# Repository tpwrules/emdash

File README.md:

# Installation Instructions

The code can be built both for an included Mac/Windows/Linux simulator and the LPC11C24 ARM microcontroller. Please follow these directions carefully to learn how to build the code. I assume you have a basic knowledge of command line operation.

## Building the Base

Building the base covers downloading the code and installing Python. Python is required to build the various data files.

#### Installing Git

The Git source control system is used to hold the code. You must install the Git client in order to download the code correctly.

* Download and install Git for your operating system from <https://git-scm.com/downloads>.
    * for the Windows installer, the default options are fine
* Clone the source code
    * open a command prompt and change to the directory you want the source to be downloaded to
    * execute `git clone https://github.com/tpwrules/emdash` to get the code

#### Installing Python

The Python scripting language is used to build data files and run the simulator. These directions have been tested with Python 3.6.6. They will most likely work with 3.5 and 3.6. Python 3.7 is not yet supported.

* Download and install the latest version of Python 3.6 for your operating system from <https://www.python.org/downloads/>
    * For the Windows installer, you must check "Add Python to Path" on the first page
    * Otherwise, the default options are fine

#### Installing Python Packages

Some Python packages are required to build the data files and run the simulator. Fortunately, Python makes them easy to install.

* Open up a command prompt.
* Run the command `python3 -m pip install pypng` or `py -3 -m pip install pypng` (on Windows)
* If python isn't found, close and re-open the command prompt.

#### Testing the Base

Now that the base has been prepared, it's time to test to make sure it works.

* Open a command prompt
* Change directories to the `dashboard` directory within the downloaded code
    * Hint: you can drag that folder into the command prompt instead of typing out its location
* Run the command `build_src_gen.py`. If you see the message `SOURCE GENERATED SUCCESSFULLY`, the base has been successfully built!

## Building for LPC11C24

Building for LPC11C24 requires a working install of the base. It does not require the simulator. I use the free MCUXpresso IDE for development on the LPC11C24. You must install it and import the project in order to deploy the code onto the chip.

#### Installing MCUXpresso
You can download the MCUXpresso 10.1.1 installer from [here](https://www.nxp.com/support/developer-resources/software-development-tools/mcuxpresso-software-and-tools/mcuxpresso-integrated-development-environment-ide:MCUXpresso-IDE?tab=Design_Tools_Tab). Click the Download button, log in with an NXP account (required), then select 10.1.1 under the Previous tab. Version 10.2 seems to be broken, so don't use it.

Run the installer using all the default options. Make a workspace in your favorite place.

#### Importing the code
Now that the projects are downloaded, they can be imported into MCUXpresso.

* Select File -> Import
* Select to import Git -> Projects from Git and click Next
* Select the Existing local repository source and click Next.
* Click Add... and then Browse...
* Select the `emdash` folder in the code you downloaded and click OK.
* Check the `emdash\.git` repository in the results list and click Finish. 
* Select the `emdash` repository in the repository list and click Next twice, then Finish. Code import is now complete.

#### Building the code
Build the code for the chip by selecting the dash_11c24 project in the left pane and clicking the hammer icon in the top bar. If everything works, you will see a blue `Build finished` in the bottom window.

You can then use the green bug icon to program the chip with the code and enter the debugger. The first time you click the button, you will be asked to create a run configuration. Double-click the `C/C++ (NXP Semiconductor)` option in the left pane to create the correct configuration, then click Debug in the bottom to start it. Once this is done, the green button will launch the correct configuration automatically.

## Building for Simulation
A custom simulator is included which runs the same code that is downloaded on the chip. Running the simulator requires a working install of the base, but does not require MCUXpresso or the other LPC11C24 stuff. It also requires a compatible install of the Visual C++ Build Tools, which use several gigabytes of disk space.

#### Installing Python Packages
The simulator requires some additional Python packages to operate.

* Open a command prompt
* Run the command `python3 -m pip install cffi numpy pygame` or `py -3 -m pip install cffi numpy pygame` (on Windows)

#### Installing Visual C++ Build Tools
The build tools provide the compiler used to compile the application for simulation. You try to compile the application to see if the tools are already installed. If they are not, an installation is necessary.

* Open a command prompt
* Change directories to the `dashboard/pc` directory inside the code
* Run the command `build_pc_app.py`. If there are no errors, you're finished building for simulation
* If it says you need to install Visual C++ 14.0, a compatible version of the build tools could not be found.
* Download the Build Tools for Visual Studio 2017 installer from <https://go.microsoft.com/fwlink/?linkid=840931>.
* Once the main installer loads, check 'Visual C++ build tools' under the 'Workloads' tab and click Install
* Wait quite a while. Once finished, try to run the script again. If it says `PC APP BUILT SUCCESSFULLY`, you've successfully built the simulator and you should be able to run it by running `pc_app.py`.

## Installing the CAN libraries
The LPC11C24 code has a bootloader and PC-based programming application so that the devices can be reprogrammed over CAN. The simulator can generate and receive CAN messages for test purposes. Both of these functionalities require the installation of CAN libraries for Python and the appropriate hardware drivers.

#### Installing the Python libraries
* Open up a command prompt.
* Run the command `python3 -m pip install python-can` or `py -3 -m pip install python-can` (on Windows)

#### Installing the Vector drivers
The program uses Vector CAN interfaces. You can try to run the programming application to see if the correct drivers are already installed. If the Vector interface drivers are not installed, they are available [here](https://vector.com/vi_downloadcenter_en.html?type=Driver&formular_treffer_submit=1). Download the latest version of "Vector Driver Setup".

* Open a command prompt
* Change directories to balsdjfsldf
* Run `the bootloader program`. If you see the error message `The Vector API has not been loaded`, the drivers must be installed. If you see a different error, continue to dkjfas;.
* Run the Vector Driver Setup installer program. Select and install the interface types you wish to use.
* Driver installation is now complete.

#### Configuring the Vector drivers
The Vector drivers require you to create an application configuration, which tells the application which hardware to use.

* Open the Windows Control Panel and select the Vector Hardware option.
* Select Application -> Add in the top bar to create a new application.
* Name the application `emdash`, set 1 CAN channel and 0 for all other types, and click OK.
* Select Application -> emdash in the left pane, then right-click on CAN 1 and select the interface you wish to use. You may have to plug in your interface first.
* Close the window. Configuration is now complete.

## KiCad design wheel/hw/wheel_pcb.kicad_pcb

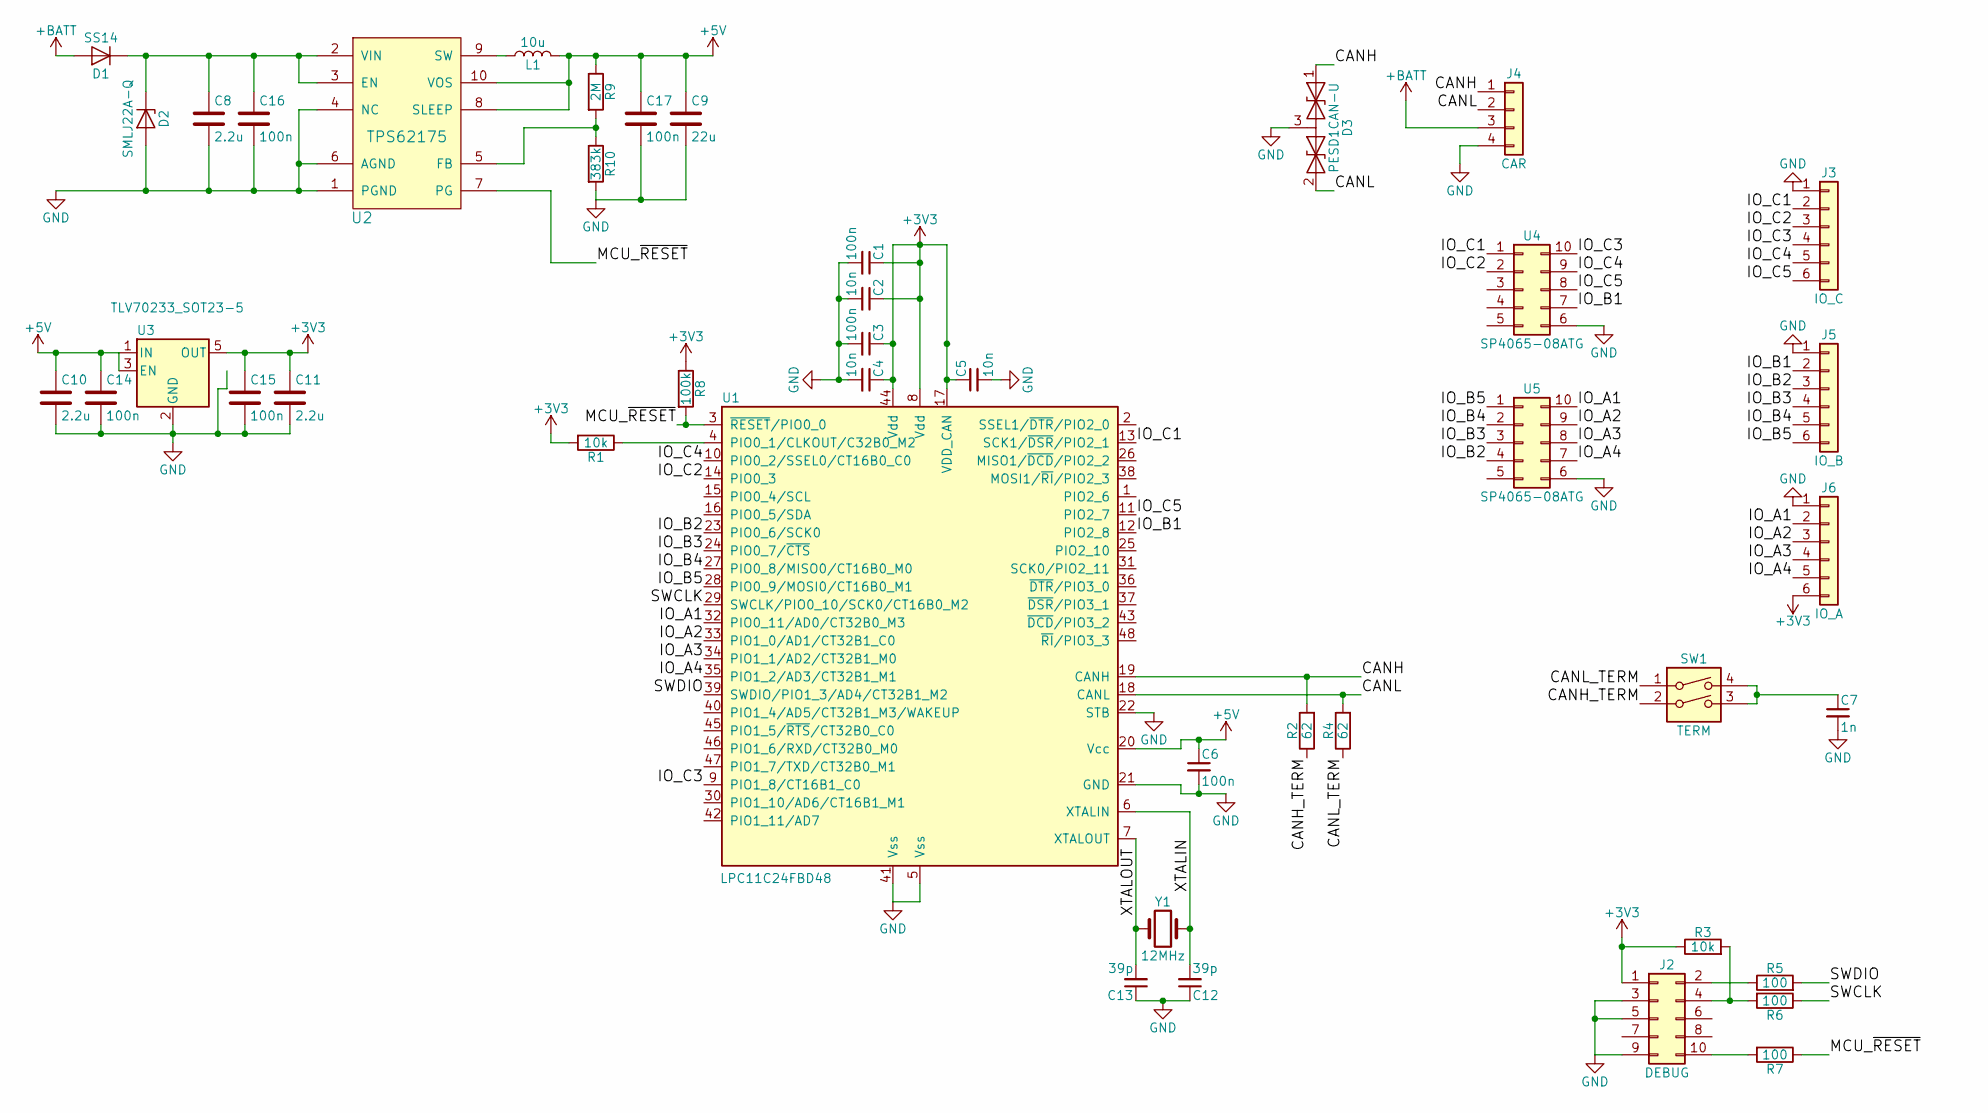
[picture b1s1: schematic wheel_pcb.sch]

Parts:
C1, C3, C6, C14, C15, C16, C17: 100n; C_0603
C2, C4, C5: 10n; C_0603
C7: 1n; C_0603
C8, C10, C11: 2.2u; C_0603
C9: 22u; C_0603
C12, C13: 39p; C_0603
D1: SS14; D_SMA_Handsoldering
D2: SMLJ22A-Q; D_SMC
D3: PESD1CAN-U; SOT-23
J2: DEBUG; Pin_Header_Angled_2x05_Pitch1.27mm_AMPHENOL_SHROUDED
J3: IO_C; Pin_Header_Angled_1x06_Pitch2.54mm
J4: CAR; Pin_Header_Angled_1x04_Pitch2.54mm
J5: IO_B; Pin_Header_Angled_1x06_Pitch2.54mm
J6: IO_A; Pin_Header_Angled_1x06_Pitch2.54mm
L1: 10u; Coilcraft_LPS4018
R1, R3: 10k; R_0603
R2, R4: 62; R_0603
R5, R6, R7: 100; R_0603
R8: 100k; R_0603
R9: 2M; R_0603
R10: 383k; R_0603
SW1: TERM; SW_DIP_x2_W7.62mm_Slide
U1: LPC11C24FBD48; LQFP-48_7x7mm_Pitch0.5mm
U2: TPS62175; DQC
U3: TLV70233_SOT23-5; SOT-23-5
U4, U5: SP4065-08ATG; MSOP-10_3x3mm_Pitch0.5mm
Y1: 12MHz; Crystal_SMD_HC49-SD

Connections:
+3V3: C1.1, C2.1, C3.1, C4.1, C5.1, C11.1, C15.1, J2.1, J6.6, R1.2, R3.1, R8.1, U1.8 (Vdd), U1.17 (VDD_CAN), U1.44 (Vdd), U3.5 (OUT)
+5V: C6.1, C9.1, C10.1, C14.1, C17.1, L1.2, R9.1, U1.20 (Vcc), U2.8 (SLEEP), U2.10 (VOS), U3.1 (IN), U3.3 (EN)
+BATT: D1.2 (A), J4.3
/CANH: D3.1 (A1), J4.1, R2.2, U1.19 (CANH)
/CANH_TERM: R2.1, SW1.2
/CANL: D3.2 (A2), J4.2, R4.2, U1.18 (CANL)
/CANL_TERM: R4.1, SW1.1
/IO_A1: J6.2, U1.32 (PIO0_11/AD0/CT32B0_M3), U5.10
/IO_A2: J6.3, U1.33 (PIO1_0/AD1/CT32B1_C0), U5.9
/IO_A3: J6.4, U1.34 (PIO1_1/AD2/CT32B1_M0), U5.8
/IO_A4: J6.5, U1.35 (PIO1_2/AD3/CT32B1_M1), U5.7
/IO_B1: J5.2, U1.12 (PIO2_8), U4.7
/IO_B2: J5.3, U1.23 (PIO0_6/SCK0), U5.4
/IO_B3: J5.4, U1.24 (PIO0_7/~CTS), U5.3
/IO_B4: J5.5, U1.27 (PIO0_8/MISO0/CT16B0_M0), U5.2
/IO_B5: J5.6, U1.28 (PIO0_9/MOSI0/CT16B0_M1), U5.1
/IO_C1: J3.2, U1.13 (SCK1/~DSR~/PIO2_1), U4.1
/IO_C2: J3.3, U1.14 (PIO0_3), U4.2
/IO_C3: J3.4, U1.9 (PIO1_8/CT16B1_C0), U4.10
/IO_C4: J3.5, U1.10 (PIO0_2/SSEL0/CT16B0_C0), U4.9
/IO_C5: J3.6, U1.11 (PIO2_7), U4.8
/MCU_~RESET: R7.1, R8.2, U1.3 (~RESET~/PIO0_0), U2.7 (PG)
/SWCLK: R6.1, U1.29 (SWCLK/PIO0_10/SCK0/CT16B0_M2)
/SWDIO: R5.2, U1.39 (SWDIO/PIO1_3/AD4/CT32B1_M2)
/XTALIN: C12.2, U1.6 (XTALIN), Y1.1
/XTALOUT: C13.2, U1.7 (XTALOUT), Y1.2
GND: C1.2, C2.2, C3.2, C4.2, C5.2, C6.2, C7.2, C8.2, C9.2, C10.2, C11.2, C12.1, C13.1, C14.2, C15.2, C16.2, C17.2, D2.2 (A), D3.3 (common), J2.3, J2.5, J2.9, J3.1, J4.4, J5.1, J6.1, R10.2, U1.5 (Vss), U1.21 (GND), U1.22 (STB), U1.41 (Vss), U2.1 (PGND), U2.4 (NC), U2.6 (AGND), U3.2 (GND), U3.4 (NC), U4.6, U5.6
unnamed: C7.1, SW1.3, SW1.4
unnamed: C8.1, C16.1, D1.1 (K), D2.1 (K), U2.2 (VIN), U2.3 (EN)
unnamed: J2.2, R5.1
unnamed: J2.4, R3.2, R6.2
unnamed: J2.10, R7.2
unnamed: L1.1, U2.9 (SW)
unnamed: R1.1, U1.4 (PIO0_1/CLKOUT/C32B0_M2)
unnamed: R9.2, R10.1, U2.5 (FB)

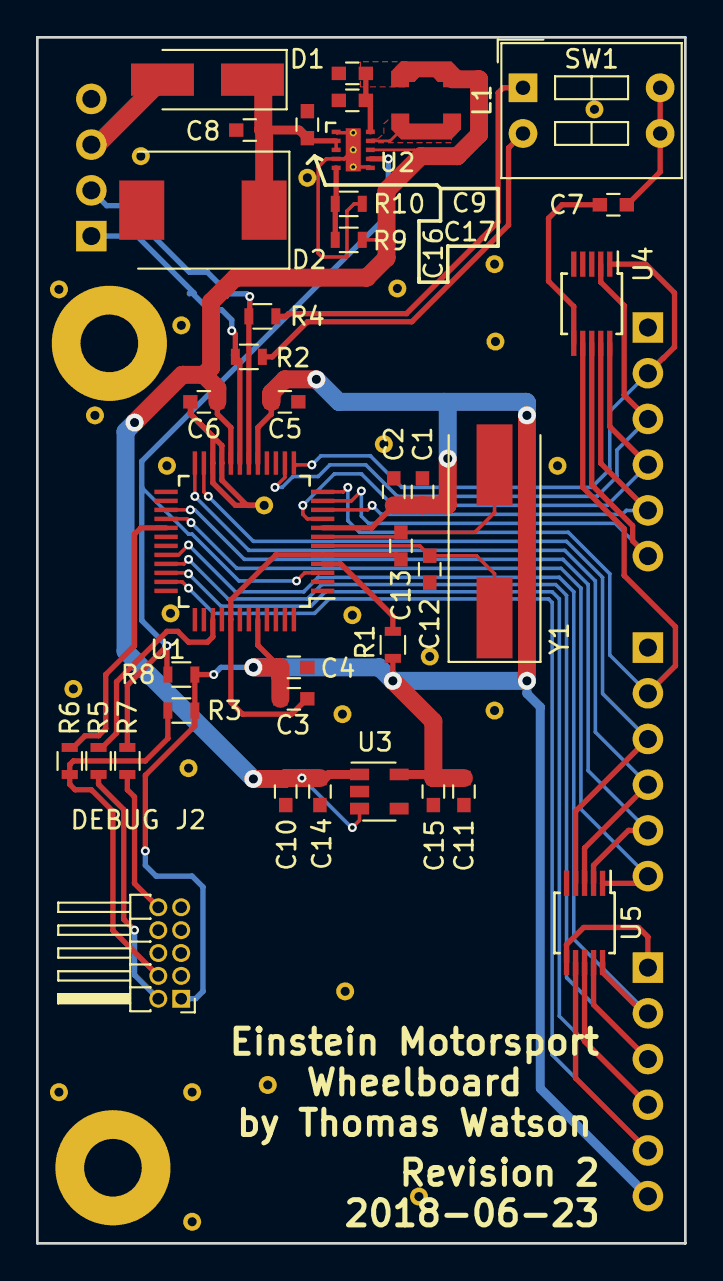
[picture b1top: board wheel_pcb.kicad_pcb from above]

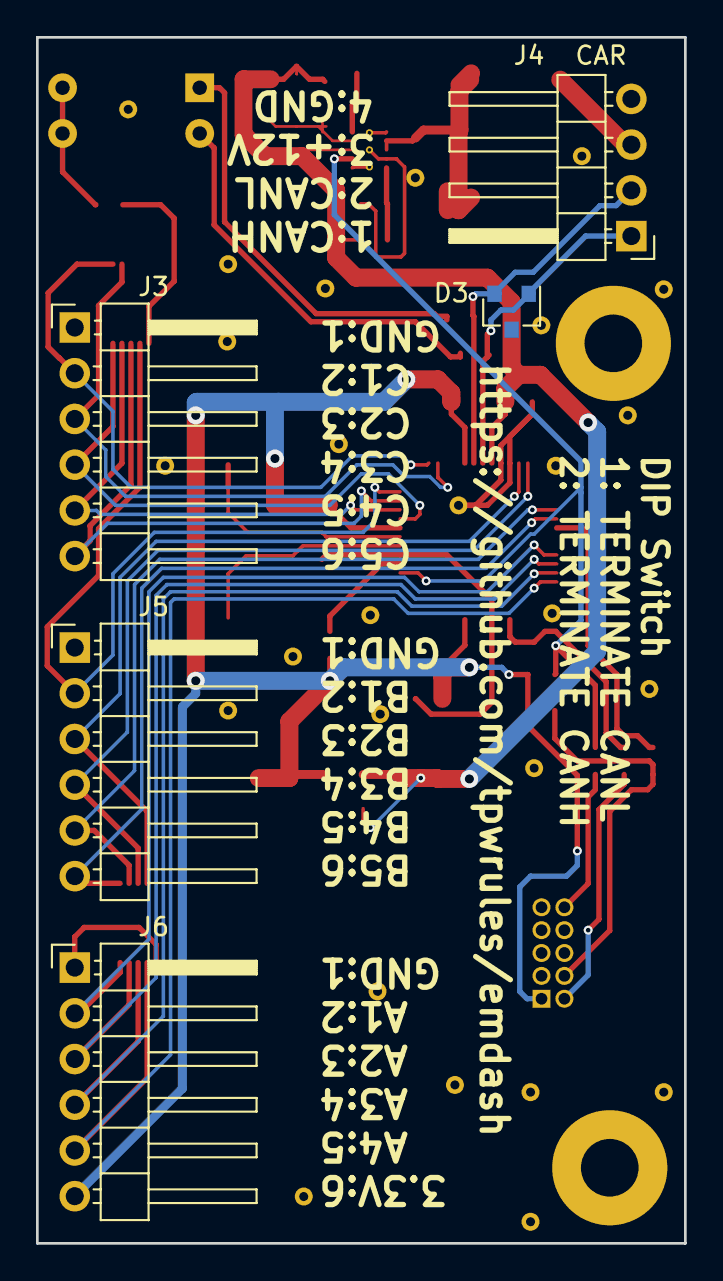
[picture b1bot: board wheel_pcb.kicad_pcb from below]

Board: 2 copper layers, 36.0 x 67.0 mm, 43 parts (5 on the bottom side), 35 nets.

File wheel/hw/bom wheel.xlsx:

Designation | Description | Mfg/# | Mouser # | RS # | Farnell # | Substitute | Quantity
C5, C4, C2 | 10nF 0603 >5V | Any | Any | Any | Any | Yes | 3
C6, C3, C1, C15, C17, C16, C14 | 100nF 0603 >5V | Any | Any | Any | Any | Yes | 7
C7 | 1nF 0603 | Any | Any | Any | Any | Yes | 1
C8, C10, C11 | 2.2uF 0603 X5R 25V | Murata GRM188R61E225ME84D | 81-GRM188R61E225ME4D | 915-9139 | 2576752 | Yes | 3
C9 | 22uF 0603 X5R 10V | Murata GRM188R61A226ME15D | 81-GRM188R61A226ME5D | 884-7258 | 2426957 | Yes | 1
C12, C13 | 39pF 0603 16V | Vishay VJ0603A390GXJPW1BC | 77-VJ0603A390GXJPBC | 652-0055 | 2496903 | Yes | 2
D1 | 40V 1A SMA Schottky Diode | Vishay SS14-E3/61T | 625-SS14-E3 | 638-7915 | 9551280 | Yes | 1
D2 | 22V 3kW Unidirectional SMA TVS Diode | Bourns SMLJ22A-Q | 652-SMLJ22A-Q | 172-3265 | 2839633 | Yes | 1
D3 | CAN bus TVS Diode | Nexperia PESD1CAN-UX | 771-PESD1CANUX | 136-4886 | 2357118 | No | 1
J2 | 2x5 1.27mm right angle shrouded male header | Samtec SHF-105-01-L-D-RA | 649-200215120001T4LF | 901-1850 | 2505002 | Yes | 1
J3, J5, J6 | 1x6 2.54mm connector | TE 281698-6 | 571-281698-6 | 532-125 | 1205994 | No | 3
J4 | 1x4 2.54mm connector | TE 281698-4 | 571-281698-4 | 532-103 | 1205992 | No | 1
L1 | 10uH SMD 1.3A 200mΩ | Coilcraft LPS4018-103MRB | 994-LPS4018-103MRB | Unavailable | 2408105 | No | 1
R2, R4 | 62Ω 0603 | Panasonic ERJ-3EKF62R0V | 667-ERJ-3EKF62R0V | 122-9377 | 2303039 | Yes | 2
R3, R1 | 10kΩ 0603 | Any | Any | Any | Any | Yes | 2
R5, R6, R7 | 100Ω 0603 | Any | Any | Any | Any | Yes | 3
R8 | 100kΩ 0603 | Any | Any | Any | Any | Yes | 1
R9 | 2MΩ 0603 1/10W 1% | Vishay CRCW06032M00FKEB | 71-CRCW06032M00FKEB | 679-0169 | 2447325 | Yes | 1
R10 | 383kΩ 0603 1/10W 1% | Yaego AC0603FR-07383KL | 603-AC0603FR-07383KL | Unavailable | 2138556 | Yes | 1
SW1 | 2 position 2.54mm DIP switch | APM NDS02V | 642-NDS02V | 877-2113 | 2858862 | No | 1
U1 | NXP LPC11C24 microcontroller | NXP LPC11C24FBD48/301 | 771-LPC11C24FBD48301 | 741-3939 | 2314754 | No | 1
U2 | 28V 0.5A switching converter | Texas Instruments TPS62175DQCR | 595-TPS62175DQCR | 825-6955 | 2255013 | No | 1
U3 | 300mA LDO 3.3v regulator | Texas Instruments TLV70233QDBVRQ1 | 595-TLV70233QDBVRQ1 | 796-8326 | 2323652 | No | 1
U4, U5 | 3.3V 20A 8x TVS array | Littelfuse SP4065-08ATG | 576-SP4065-08ATG | Unavailable | 2762920 | No | 2
Y1 | 12MHz 18pF HC49/US SMD | ABLS-12.000MHZ-B2-T | 815-ABLS-12-B2 | 703-1809 | 1652551 | Yes | 1

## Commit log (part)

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2018-04-10 yay macos
2018-04-10 add bootsplash picture
2018-04-11 add very basic interrupt support plus the timer interrupt
2018-04-12 add graphics output
2018-04-12 add animated RPM display
2018-04-12 upgrade timer to 10ms
2018-04-12 improve timing accuracy
2018-04-15 strictify prototypes to make clang happy
2018-04-15 overhaul screen infrastructure and also the c->py interface
2018-04-15 flash entire screen for upshift instead of just gear indicator
2018-04-15 add real interrupt system
2018-04-15 add list of pictures instead of just hardcoding the one
2018-04-15 show splash for a second on boot
2018-04-16 add canvar system data files
2018-04-16 improve canvar system by making all vars uint32_t and by generating callback prototypes programatically
2018-04-16 call canvar callbacks in main loop instead of from interrupt context
2018-04-16 rename gear_ functions to drive_
2018-04-16 add placeholders for important info
2018-04-17 extend canvar to support multiple variables per message
2018-04-17 add can messages for important figures
2018-04-17 add nice python interface for sending can stuff
2018-04-17 add pretty warning icons
2018-04-18 make icons show up under warning conditions
2018-04-18 display some test gears
2018-04-18 move gear and rpm into drive file
2018-04-18 parameterize warning thresholds
2018-04-18 add battery voltage
2018-04-18 tweak inversion to be a little less ugly
2018-04-18 show rpm also when blinking
2018-04-18 move warning icons to their own file
2018-04-19 add snowflake icon to indicate oil is cold
2018-04-19 add real gear number font
2018-04-19 only include pictures of used gears
2018-04-19 finally fix godawful font on bootsplash
2018-04-19 pretty up albert's face
2018-04-19 add real radio and up/down shift icons
2018-04-19 disable upshift blinking in sim
2018-04-20 graphics tweaks
2018-04-20 connect auto mode and launch control to CAN
2018-04-21 write out picture data
2018-04-21 add simple compression to pictures
2018-04-21 add another compression method to save a couple hundo bytes
2018-04-21 oops
2018-04-21 show dash and wheel version on screen
2018-04-21 add a lock to the canvar interface so nothing bad happens
2018-04-21 implement radio button
2018-04-21 implement traction control knob
2018-04-21 implement app modes
2018-04-21 automatically switch away from showing version after a short delay
2018-04-22 be sure to only call the next mode with interrupts already enabled
2018-04-22 add mode with remaining parameters
2018-04-22 rework interrupt handling to be closer to correct
2018-04-22 fix some warnings
2018-04-22 avoid drawing warning icons excessively
2018-04-22 move generated source into its own directory
2018-04-22 add basic mcuxpresso project
2018-04-22 amend
2018-04-22 add interrupt framework and dummy screen interface
2018-04-22 random change apparently
2018-04-22 add kicad ignore files
2018-04-22 add LCD and debug connectors
2018-04-22 set up lcd shape as the pcb
2018-04-22 work on laying out LCD connector
2018-04-22 apply new ranges and limits
2018-04-22 lol what
2018-04-24 label a couple more required pins
2018-04-27 initialize gpio without calling into board lib
2018-04-27 add lcd driver which doesn't really work
2018-04-27 update screen defines to reflect actual screen memory
2018-04-27 clean up init
2018-04-27 100x turbo
2018-04-27 make driver grown up by having actual api
2018-04-27 ward off silicon bug
2018-04-27 show text and graphics, a little
2018-04-27 uh turns out graphics bytes are 6x1 not 8x1 so change real hw for that
2018-04-27 update for larger graphics pages
2018-04-27 fix graphics for 6x1
2018-04-27 6x1 the rectangles in sim
2018-04-28 fix prebuild not running before main build
2018-04-28 remove scren demo now that the screen is working
2018-04-28 add ability to generate can message logs from sim
2018-04-28 convert can log to c file for later replay
2018-04-28 respect picture inversion
2018-04-28 fix gear pictures so that there's no longer overlap
2018-04-28 put marker on rpm bar approx at upshift point
2018-04-28 clean t6963 api a bit
2018-04-28 update screen driver to use auto mode for 2x turbo boost
2018-04-29 add option to turn off auto mode cause it's currently crashy
2018-04-29 turns out it was probably a logic level issue; drive display module at 3v3 instead
2018-04-29 update connectors for the lcd actually used
2018-04-30 build app library directly with cffi instead of into its own so
2018-05-01 remove shell script from src gen process
2018-05-01 make pc app be more sensible with paths
2018-05-01 add shebang to pc app builder
2018-05-01 fix various compiler warnings
2018-05-01 completely sever connection to never used board lib
2018-05-01 rgh windows
2018-05-01 add readme
2018-05-04 add new compression algorithm but don't use it
2018-05-04 dash now receives messages from actual can hardware
2018-05-04 add completely untested option to send canbus out irl
2018-05-04 make can actually work
2018-05-04 ignore build artifacts on windows
2018-05-05 improve picture compression
2018-05-07 add schematic symbol for lmz21700 power module
2018-05-07 add tps62175 which we are actually using
2018-05-07 add 3v3 power supply
2018-05-07 add crystal to nxp
2018-05-08 add led backlight 'driver'
2018-05-09 more parts shopping
2018-05-09 add footprint for TI power chip
2018-05-09 add footprint for inductor
2018-05-14 reset automatically when power isn't good
2018-05-14 lay out passives and xtal around the micro
2018-05-14 route out lcd connector
2018-05-14 route power
2018-05-15 correct custom component courtyards
2018-05-15 make shrouded version of programming connector
2018-05-15 adjust vars for new vehicle
2018-05-15 update battery voltage func
2018-05-15 introduce concept of multiplexing canvars. sigh
2018-05-15 add multiplexing to python canvar interface
2018-05-15 relabel temperature measurement according to jonas
2018-05-16 use 4 position connector for car interface
2018-05-16 add jumpers to selectively terminate can bus
2018-05-16 change termination jumpers to dip switches
2018-05-16 misc changes to part numbers and such
2018-05-18 add mounting holes to match lcd
2018-05-18 crunch board a bunch
2018-05-18 scrunch up 3.3v
2018-05-18 improve grounding
2018-05-18 another 0.1 inches
2018-05-18 clean up pcb
2018-05-18 copy dashboard to wheelboard
2018-05-18 preliminarily lay out and pin wheel connectors
2018-05-19 relabel i/o with less lcd names
2018-05-19 clean up button bus
2018-05-19 silkscreen
2018-05-19 add mounting holes to wheelboard
2018-05-19 wheel revision one gerbers
2018-05-19 its gerber time almost for the dashbaord
2018-05-27 change can id to var lookup to hashmap to save mega flash
2018-05-27 change mode changes a little for future improvements
2018-05-27 oops, version mode func should be itself
2018-05-27 write out canvar IDs to def header
2018-05-27 add ability to make canvars with no bus ID
2018-05-27 change how mode switching works so forcing a mode is easier
2018-05-27 add can bus error display
2018-05-28 misc time and space improvements
2018-06-11 prepare rectangles to be able to start on arbitrary pixels
2018-06-11 get pixeltangles working in simulator
2018-06-15 make rectangles a bit more efficient
2018-06-16 improve macros to hopefully reduce future surprises
2018-06-16 create project for wheel firmware
2018-06-16 add wheel demo which just spams the version ID
2018-06-16 calculate and transmit actual version
2018-06-17 spec out button defs
2018-06-17 generate button data tables
2018-06-17 and get rid of it
2018-06-17 add code to read the button
2018-06-17 change default release time for better tapping
2018-06-17 add traction control knob
2018-06-18 add way to make most of the screen zero
2018-06-18 fix pics maybe
2018-06-18 add draft of manual aimed at programmers
2018-06-18 rework implementation of None canvar callbacks
2018-06-18 fix it
2018-06-19 prevent timer interrupts from piling up
2018-06-19 add draft of customizer manual
2018-06-20 add protection circuitry
2018-06-20 make 2 position slide switches instead of 4
2018-06-20 quick name change
2018-06-21 minor use note
2018-06-21 update with var names and more information
2018-06-22 pretty much finish wheel layout
2018-06-23 draft layout for dash board
2018-06-23 redo it but this time put the protection next to the input
2018-06-23 fix silkscreen
2018-06-23 add github link to boards
2018-06-23 shrink crystal traces to reduce risk of solder accidents
2018-06-23 bump revision to 2 and plot it
2018-06-24 clarify modes and file paths
2018-06-24 improve customizer manual
2018-06-25 update bom for new revision
2018-06-26 update rpm limits to desired values
2018-06-26 update message defs according to actual car
2018-07-01 change temperatures to use C and also degrees symbol
2018-07-02 add bootloader which doesn't really do anything yet
2018-07-02 get rid of code read protection since the bootloader handles it now
2018-07-02 reserve required RAM space for iap routines
2018-07-02 get canbus up
2018-07-03 make boot code able to reboot the chip
2018-07-03 implement hello at beginning of transaction
2018-07-03 implement flash operations so bootloader actually works
2018-07-03 better define how to get into bootloader
2018-07-04 put less likely to change functions in after_vectors section
2018-07-04 add gitignore for system ids so change doesn't get stuck in repo
2018-07-04 update that didn't work as expected
2018-07-04 somehow forgot that one
2018-07-04 polish some misc stuff
2018-07-04 implement bootloader protocol timeout
2018-07-04 integrate bootloader into dashboard
2018-07-04 integrate bootloader into wheelboard
2018-07-04 rework calling shell from eclipse cause of weirdities in 10.2
2018-07-04 fix links and tweak directions
2018-07-09 put system id in header so user doesn't have to choose when bootloading
2018-07-09 forgot to move that
2018-07-09 more
2018-07-09 make bootload program actually work with new changes
2018-07-09 add lpc chip lib to repo so it doesn't have to be tracked down and changed etc
2018-07-09 reinclude language settings files apparently
2018-07-09 add rate printout to bootload test to measure bus utilization
2018-07-09 misc obsessing over bootloader related code
2018-07-09 implement new, reasonable bootloader program
2018-07-09 actually implement bus utilization limiting
2018-07-09 expand on some error messages
2018-07-09 fix hysteresis when powered on in the dead zone
2018-07-10 avoid bothering application with bootloader-related messages
2018-07-10 put dash systick handler in platform code cause that's really where it does its work
2018-07-10 move cpu display to canvar status page
2018-07-10 tweak wordsing
2018-07-10 add hysteresis to integer values so they stop wiggling
2018-07-11 document ADC channels on button board
2018-07-11 move docs out of dashboard
2018-07-14 begin writing manual for wheelboard
2018-07-18 make debouncer look for the same button state instead of just one that's not the current one
2018-07-18 add functionality for bootloader to say if application is valid
2018-07-18 add read flash command to bootloader so that pc script can show version
2018-07-18 add checksumming and version to bootloader also
2018-07-18 add boot rescue mode for if app is messed up
2018-07-18 oops remove boot version file from being tracked
2018-07-18 make version only based on files relevant to that app
2018-07-18 another nitpick commit
2018-07-18 wow another nitpick commit
2018-07-18 show git metadata for version instead of just boring commit hash
2018-07-18 niceify a couple of error messages in pc boot
2018-07-19 remove rescue mode for programming and just make regular mode that
2018-07-19 rename pc programmer with actual name
2018-07-19 move rescue constants to boot cause they shouldn't be touched by app
2018-07-19 fix irq redirect for vectors >= 128
2018-07-19 add timeout in bootloader on message transmission too
2018-07-20 clean up picture encoding
2018-07-20 misc cleanup and nitpicking to wheelboard
2018-07-20 turn down bounce time on tc knob to feel more responsive
2018-07-20 clean up screen show/clear functions a tad
2018-07-20 fix splinge
2018-07-21 pre=stringify version to save space
